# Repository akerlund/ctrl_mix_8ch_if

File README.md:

# ctrl_mix_8ch_if
An eight channel controller board for custom use

Each channel has one slider, two encoders, one switch and four LEDs. The PCB has got two potentiometers on each top corner and  4 LED bars for signal visualization. On the back there are analogue MUXes and LED drivers.

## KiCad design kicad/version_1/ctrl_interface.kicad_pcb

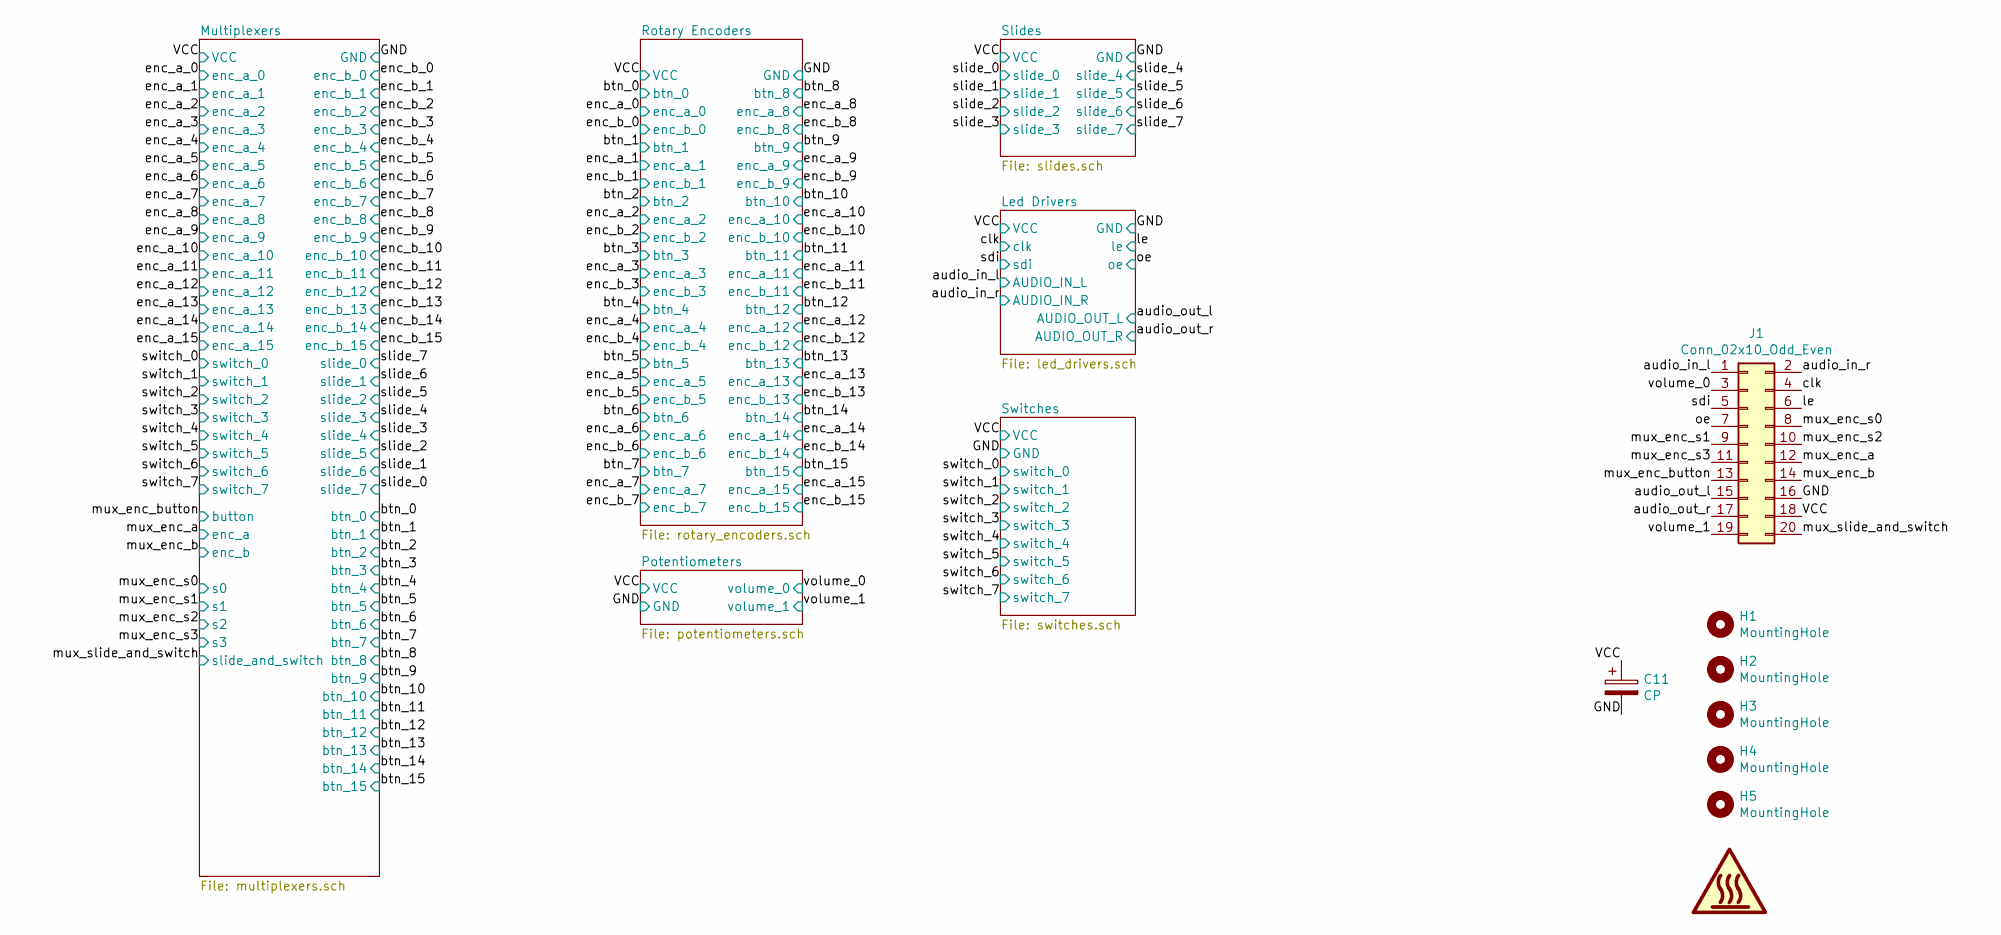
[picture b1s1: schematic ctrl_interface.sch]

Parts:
C11: CP; CP_Elec_5x5.7
H1, H2, H3, H4, H5: MountingHole; MountingHole_3mm_Pad_Via
J1: Conn_02x10_Odd_Even; PinSocket_2x10_P2.54mm_Vertical

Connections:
/GND: C11.2, J1.16; also elsewhere on the board
/VCC: C11.1, J1.18; also elsewhere on the board
/audio_in_l: J1.1; also elsewhere on the board
/audio_in_r: J1.2; also elsewhere on the board
/audio_out_l: J1.15; also elsewhere on the board
/audio_out_r: J1.17; also elsewhere on the board
/clk: J1.4; also elsewhere on the board
/le: J1.6; also elsewhere on the board
/mux_enc_a: J1.12; also elsewhere on the board
/mux_enc_b: J1.14; also elsewhere on the board
/mux_enc_button: J1.13; also elsewhere on the board
/mux_enc_s0: J1.8; also elsewhere on the board
/mux_enc_s1: J1.9; also elsewhere on the board
/mux_enc_s2: J1.10; also elsewhere on the board
/mux_enc_s3: J1.11; also elsewhere on the board
/mux_slide_and_switch: J1.20; also elsewhere on the board
/oe: J1.7; also elsewhere on the board
/sdi: J1.5; also elsewhere on the board
/volume_0: J1.3; also elsewhere on the board
/volume_1: J1.19; also elsewhere on the board

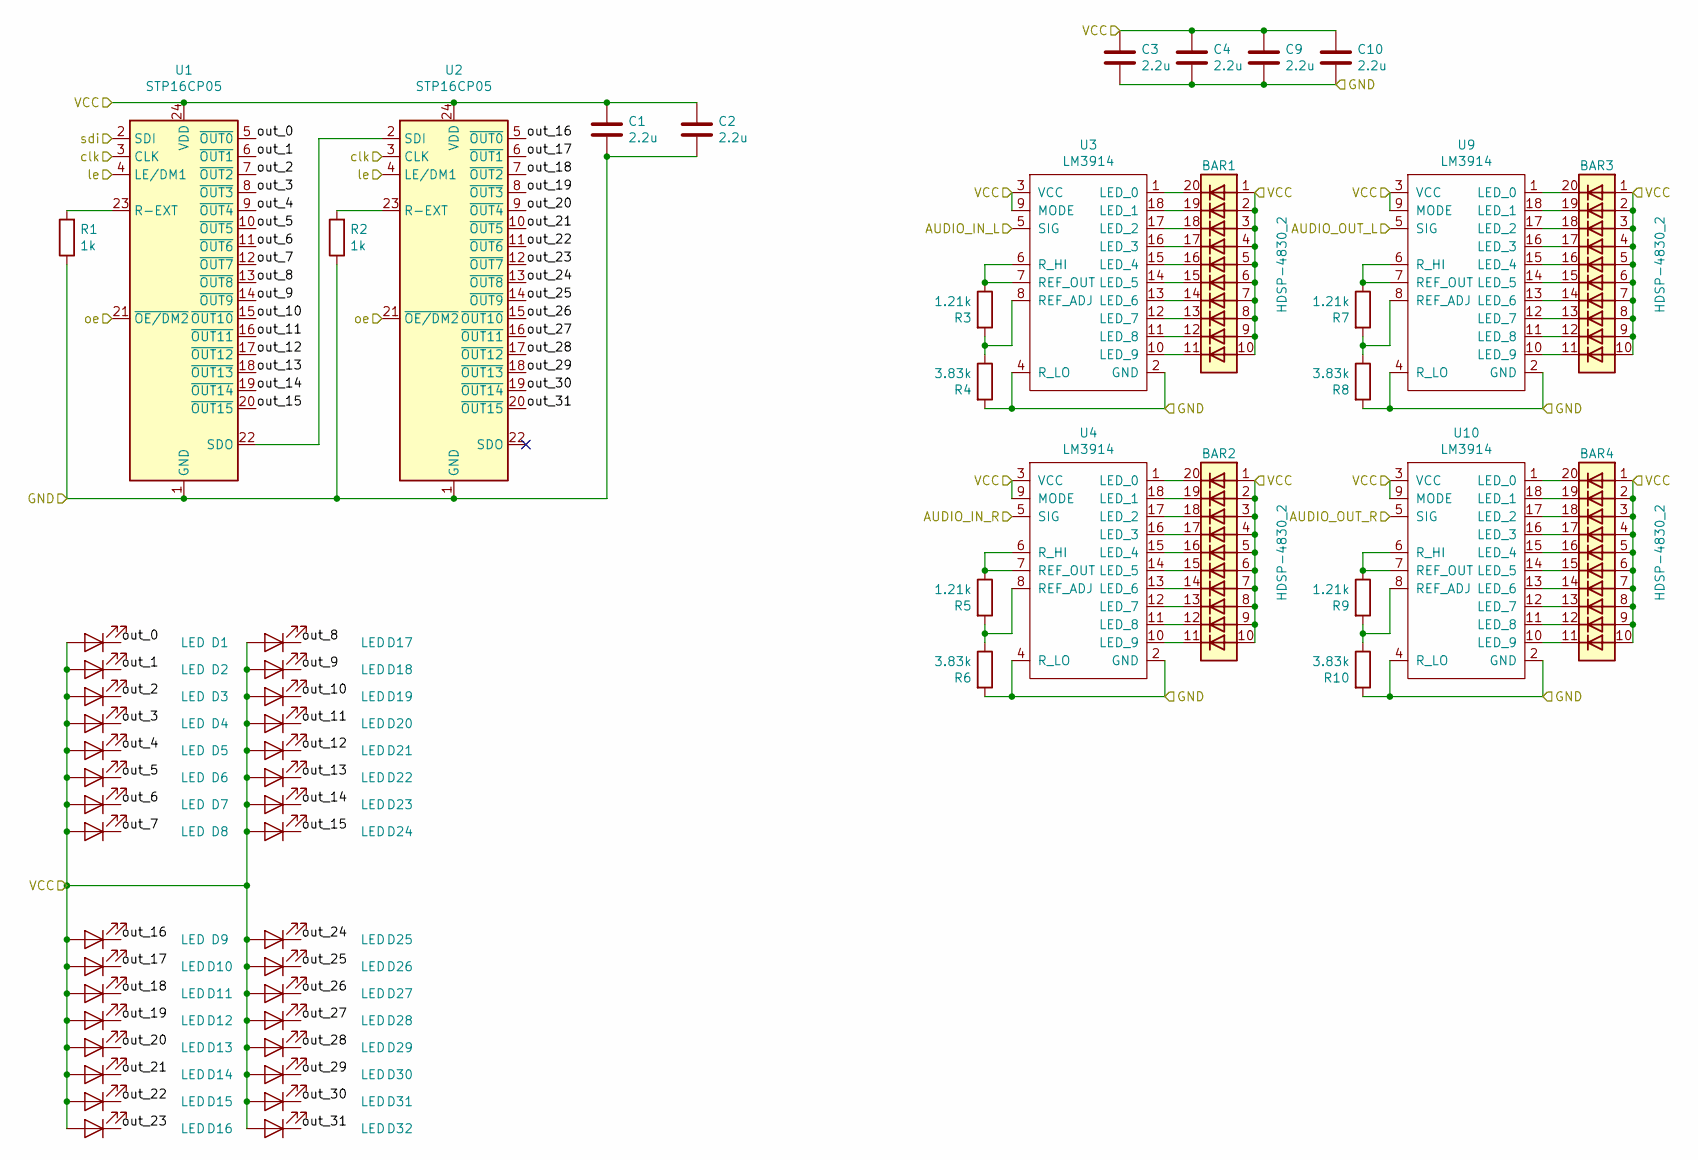
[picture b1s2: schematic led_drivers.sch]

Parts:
BAR1, BAR2, BAR3, BAR4: HDSP-4830_2; HDSP-4830
C1, C2, C3, C4, C9, C10: 2.2u; C_0603_1608Metric
D1, D2, D3, D4, D5, D6, D7, D8, D9, D10, D11, D12, D13, D14, D15, D16, D17, D18, D19, D20, D21, D22, D23, D24, D25, D26, D27, D28, D29, D30, D31, D32: LED; LED_0805_2012Metric
R1, R2: 1k; R_0603_1608Metric
R3, R5, R7, R9: 1.21k; R_0603_1608Metric
R4, R6, R8, R10: 3.83k; R_0603_1608Metric
U1, U2: STP16CP05; SSOP-24_3.9x8.7mm_P0.635mm
U3, U4, U9, U10: LM3914; DIP-18_W7.62mm

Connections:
/GND: C1.2, C2.2, C3.2, C4.2, C9.2, C10.2, R1.1, R2.1, R4.2, R6.2, R8.2, R10.2, U1.1 (GND), U2.1 (GND), U3.2 (GND), U3.4 (R_LO), U4.2 (GND), U4.4 (R_LO), U9.2 (GND), U9.4 (R_LO), U10.2 (GND), U10.4 (R_LO); also elsewhere on the board
/Led Drivers/out_0: D1.1 (K), U1.5 (~OUT0)
/Led Drivers/out_1: D2.1 (K), U1.6 (~OUT1)
/Led Drivers/out_2: D3.1 (K), U1.7 (~OUT2)
/Led Drivers/out_3: D4.1 (K), U1.8 (~OUT3)
/Led Drivers/out_4: D5.1 (K), U1.9 (~OUT4)
/Led Drivers/out_5: D6.1 (K), U1.10 (~OUT5)
/Led Drivers/out_6: D7.1 (K), U1.11 (~OUT6)
/Led Drivers/out_7: D8.1 (K), U1.12 (~OUT7)
/Led Drivers/out_8: D17.1 (K), U1.13 (~OUT8)
/Led Drivers/out_9: D18.1 (K), U1.14 (~OUT9)
/Led Drivers/out_10: D19.1 (K), U1.15 (~OUT10)
/Led Drivers/out_11: D20.1 (K), U1.16 (~OUT11)
/Led Drivers/out_12: D21.1 (K), U1.17 (~OUT12)
/Led Drivers/out_13: D22.1 (K), U1.18 (~OUT13)
/Led Drivers/out_14: D23.1 (K), U1.19 (~OUT14)
/Led Drivers/out_15: D24.1 (K), U1.20 (~OUT15)
/Led Drivers/out_16: D9.1 (K), U2.5 (~OUT0)
/Led Drivers/out_17: D10.1 (K), U2.6 (~OUT1)
/Led Drivers/out_18: D11.1 (K), U2.7 (~OUT2)
/Led Drivers/out_19: D12.1 (K), U2.8 (~OUT3)
/Led Drivers/out_20: D13.1 (K), U2.9 (~OUT4)
/Led Drivers/out_21: D14.1 (K), U2.10 (~OUT5)
/Led Drivers/out_22: D15.1 (K), U2.11 (~OUT6)
/Led Drivers/out_23: D16.1 (K), U2.12 (~OUT7)
/Led Drivers/out_24: D25.1 (K), U2.13 (~OUT8)
/Led Drivers/out_25: D26.1 (K), U2.14 (~OUT9)
/Led Drivers/out_26: D27.1 (K), U2.15 (~OUT10)
/Led Drivers/out_27: D28.1 (K), U2.16 (~OUT11)
/Led Drivers/out_28: D29.1 (K), U2.17 (~OUT12)
/Led Drivers/out_29: D30.1 (K), U2.18 (~OUT13)
/Led Drivers/out_30: D31.1 (K), U2.19 (~OUT14)
/Led Drivers/out_31: D32.1 (K), U2.20 (~OUT15)
/VCC: BAR1.1 (A), BAR1.2 (A), BAR1.3 (A), BAR1.4 (A), BAR1.5 (A), BAR1.6 (A), BAR1.7 (A), BAR1.8 (A), BAR1.9 (A), BAR1.10 (A), BAR2.1 (A), BAR2.2 (A), BAR2.3 (A), BAR2.4 (A), BAR2.5 (A), BAR2.6 (A), BAR2.7 (A), BAR2.8 (A), BAR2.9 (A), BAR2.10 (A), BAR3.1 (A), BAR3.2 (A), BAR3.3 (A), BAR3.4 (A), BAR3.5 (A), BAR3.6 (A), BAR3.7 (A), BAR3.8 (A), BAR3.9 (A), BAR3.10 (A), BAR4.1 (A), BAR4.2 (A), BAR4.3 (A), BAR4.4 (A), BAR4.5 (A), BAR4.6 (A), BAR4.7 (A), BAR4.8 (A), BAR4.9 (A), BAR4.10 (A), C1.1, C2.1, C3.1, C4.1, C9.1, C10.1, D1.2 (A), D2.2 (A), D3.2 (A), D4.2 (A), D5.2 (A), D6.2 (A), D7.2 (A), D8.2 (A), D9.2 (A), D10.2 (A), D11.2 (A), D12.2 (A), D13.2 (A), D14.2 (A), D15.2 (A), D16.2 (A), D17.2 (A), D18.2 (A), D19.2 (A), D20.2 (A), D21.2 (A), D22.2 (A), D23.2 (A), D24.2 (A), D25.2 (A), D26.2 (A), D27.2 (A), D28.2 (A), D29.2 (A), D30.2 (A), D31.2 (A), D32.2 (A), U1.24 (VDD), U2.24 (VDD), U3.3 (VCC), U3.9 (MODE), U4.3 (VCC), U4.9 (MODE), U9.3 (VCC), U9.9 (MODE), U10.3 (VCC), U10.9 (MODE); also elsewhere on the board
/audio_in_l: U3.5 (SIG); also elsewhere on the board
/audio_in_r: U4.5 (SIG); also elsewhere on the board
/audio_out_l: U9.5 (SIG); also elsewhere on the board
/audio_out_r: U10.5 (SIG); also elsewhere on the board
/clk: U1.3 (CLK), U2.3 (CLK); also elsewhere on the board
/le: U1.4 (LE/DM1), U2.4 (LE/DM1); also elsewhere on the board
/oe: U1.21 (~OE/DM2), U2.21 (~OE/DM2); also elsewhere on the board
/sdi: U1.2 (SDI); also elsewhere on the board
unnamed: BAR1.11 (K), U3.10 (LED_9)
unnamed: BAR1.12 (K), U3.11 (LED_8)
unnamed: BAR1.13 (K), U3.12 (LED_7)
unnamed: BAR1.14 (K), U3.13 (LED_6)
unnamed: BAR1.15 (K), U3.14 (LED_5)
unnamed: BAR1.16 (K), U3.15 (LED_4)
unnamed: BAR1.17 (K), U3.16 (LED_3)
unnamed: BAR1.18 (K), U3.17 (LED_2)
unnamed: BAR1.19 (K), U3.18 (LED_1)
unnamed: BAR1.20 (K), U3.1 (LED_0)
unnamed: BAR2.11 (K), U4.10 (LED_9)
unnamed: BAR2.12 (K), U4.11 (LED_8)
unnamed: BAR2.13 (K), U4.12 (LED_7)
unnamed: BAR2.14 (K), U4.13 (LED_6)
unnamed: BAR2.15 (K), U4.14 (LED_5)
unnamed: BAR2.16 (K), U4.15 (LED_4)
unnamed: BAR2.17 (K), U4.16 (LED_3)
unnamed: BAR2.18 (K), U4.17 (LED_2)
unnamed: BAR2.19 (K), U4.18 (LED_1)
unnamed: BAR2.20 (K), U4.1 (LED_0)
unnamed: BAR3.11 (K), U9.10 (LED_9)
unnamed: BAR3.12 (K), U9.11 (LED_8)
unnamed: BAR3.13 (K), U9.12 (LED_7)
unnamed: BAR3.14 (K), U9.13 (LED_6)
unnamed: BAR3.15 (K), U9.14 (LED_5)
unnamed: BAR3.16 (K), U9.15 (LED_4)
unnamed: BAR3.17 (K), U9.16 (LED_3)
unnamed: BAR3.18 (K), U9.17 (LED_2)
unnamed: BAR3.19 (K), U9.18 (LED_1)
unnamed: BAR3.20 (K), U9.1 (LED_0)
unnamed: BAR4.11 (K), U10.10 (LED_9)
unnamed: BAR4.12 (K), U10.11 (LED_8)
unnamed: BAR4.13 (K), U10.12 (LED_7)
unnamed: BAR4.14 (K), U10.13 (LED_6)
unnamed: BAR4.15 (K), U10.14 (LED_5)
unnamed: BAR4.16 (K), U10.15 (LED_4)
unnamed: BAR4.17 (K), U10.16 (LED_3)
unnamed: BAR4.18 (K), U10.17 (LED_2)
unnamed: BAR4.19 (K), U10.18 (LED_1)
unnamed: BAR4.20 (K), U10.1 (LED_0)
unnamed: R1.2, U1.23 (R-EXT)
unnamed: R2.2, U2.23 (R-EXT)
unnamed: R3.1, U3.6 (R_HI), U3.7 (REF_OUT)
unnamed: R3.2, R4.1, U3.8 (REF_ADJ)
unnamed: R5.1, U4.6 (R_HI), U4.7 (REF_OUT)
unnamed: R5.2, R6.1, U4.8 (REF_ADJ)
unnamed: R7.1, U9.6 (R_HI), U9.7 (REF_OUT)
unnamed: R7.2, R8.1, U9.8 (REF_ADJ)
unnamed: R9.1, U10.6 (R_HI), U10.7 (REF_OUT)
unnamed: R9.2, R10.1, U10.8 (REF_ADJ)
unnamed: U1.22 (SDO), U2.2 (SDI)

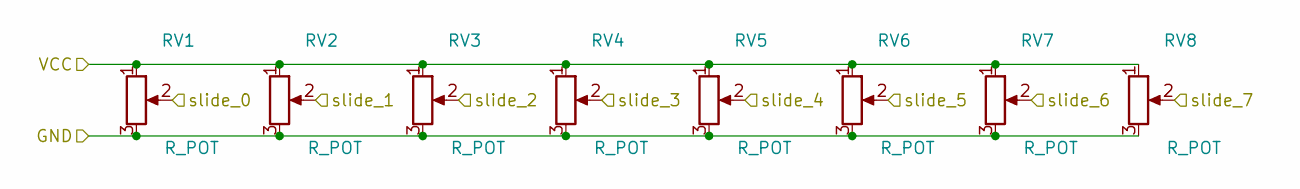
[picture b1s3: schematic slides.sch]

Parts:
RV1, RV2, RV3, RV4, RV5, RV6, RV7, RV8: R_POT; slide_pot_PS6010MA1B

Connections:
/GND: RV1.3, RV2.3, RV3.3, RV4.3, RV5.3, RV6.3, RV7.3, RV8.3; also elsewhere on the board
/VCC: RV1.1, RV2.1, RV3.1, RV4.1, RV5.1, RV6.1, RV7.1, RV8.1; also elsewhere on the board
/slide_0: RV1.2; also elsewhere on the board
/slide_1: RV2.2; also elsewhere on the board
/slide_2: RV3.2; also elsewhere on the board
/slide_3: RV4.2; also elsewhere on the board
/slide_4: RV5.2; also elsewhere on the board
/slide_5: RV6.2; also elsewhere on the board
/slide_6: RV7.2; also elsewhere on the board
/slide_7: RV8.2; also elsewhere on the board

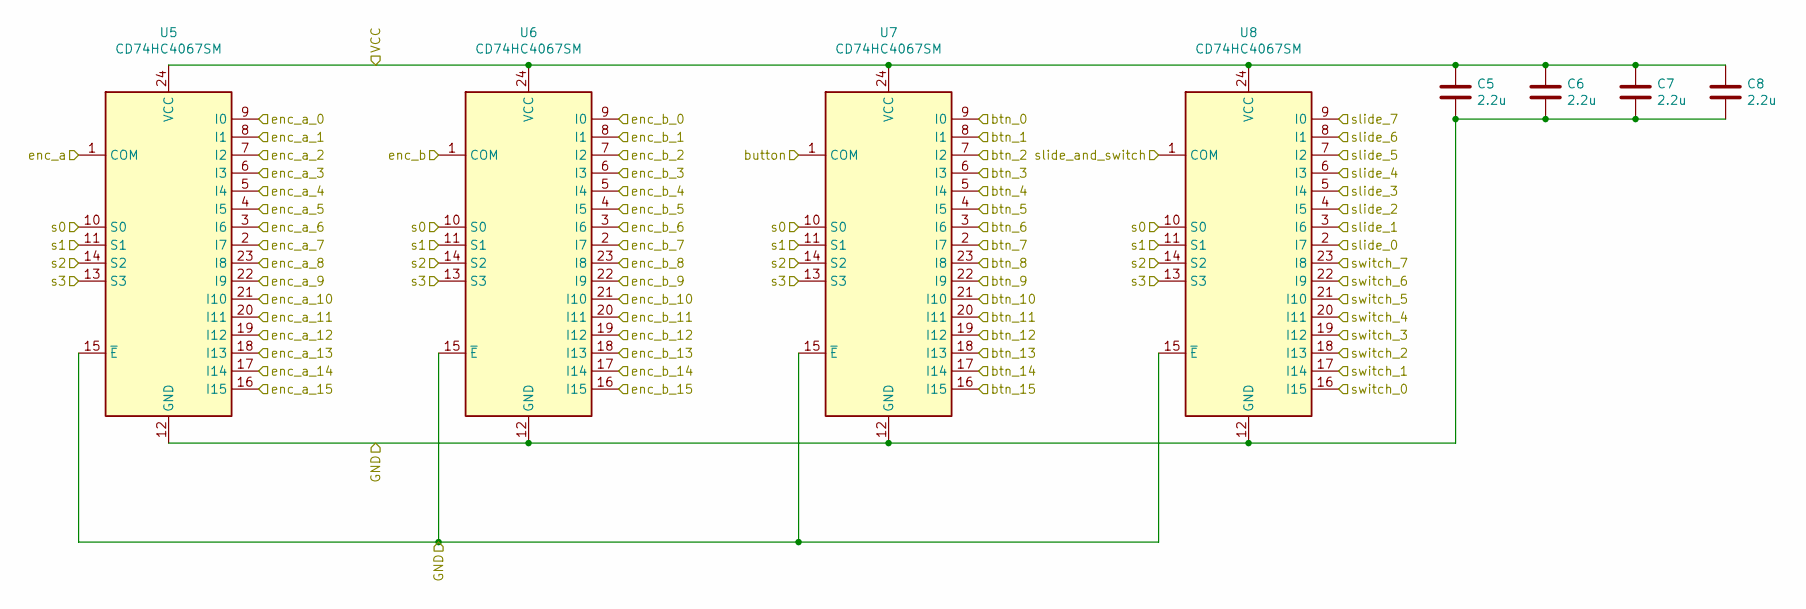
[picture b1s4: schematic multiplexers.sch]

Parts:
C5, C6, C7, C8: 2.2u; C_0603_1608Metric
U5, U6, U7, U8: CD74HC4067SM; SSOP-24_5.3x8.2mm_P0.65mm

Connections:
/GND: C5.2, C6.2, C7.2, C8.2, U5.12 (GND), U5.15 (~E), U6.12 (GND), U6.15 (~E), U7.12 (GND), U7.15 (~E), U8.12 (GND), U8.15 (~E); also elsewhere on the board
/VCC: C5.1, C6.1, C7.1, C8.1, U5.24 (VCC), U6.24 (VCC), U7.24 (VCC), U8.24 (VCC); also elsewhere on the board
/btn_0: U7.9 (I0); also elsewhere on the board
/btn_1: U7.8 (I1); also elsewhere on the board
/btn_2: U7.7 (I2); also elsewhere on the board
/btn_3: U7.6 (I3); also elsewhere on the board
/btn_4: U7.5 (I4); also elsewhere on the board
/btn_5: U7.4 (I5); also elsewhere on the board
/btn_6: U7.3 (I6); also elsewhere on the board
/btn_7: U7.2 (I7); also elsewhere on the board
/btn_8: U7.23 (I8); also elsewhere on the board
/btn_9: U7.22 (I9); also elsewhere on the board
/btn_10: U7.21 (I10); also elsewhere on the board
/btn_11: U7.20 (I11); also elsewhere on the board
/btn_12: U7.19 (I12); also elsewhere on the board
/btn_13: U7.18 (I13); also elsewhere on the board
/btn_14: U7.17 (I14); also elsewhere on the board
/btn_15: U7.16 (I15); also elsewhere on the board
/enc_a_0: U5.9 (I0); also elsewhere on the board
/enc_a_1: U5.8 (I1); also elsewhere on the board
/enc_a_2: U5.7 (I2); also elsewhere on the board
/enc_a_3: U5.6 (I3); also elsewhere on the board
/enc_a_4: U5.5 (I4); also elsewhere on the board
/enc_a_5: U5.4 (I5); also elsewhere on the board
/enc_a_6: U5.3 (I6); also elsewhere on the board
/enc_a_7: U5.2 (I7); also elsewhere on the board
/enc_a_8: U5.23 (I8); also elsewhere on the board
/enc_a_9: U5.22 (I9); also elsewhere on the board
/enc_a_10: U5.21 (I10); also elsewhere on the board
/enc_a_11: U5.20 (I11); also elsewhere on the board
/enc_a_12: U5.19 (I12); also elsewhere on the board
/enc_a_13: U5.18 (I13); also elsewhere on the board
/enc_a_14: U5.17 (I14); also elsewhere on the board
/enc_a_15: U5.16 (I15); also elsewhere on the board
/enc_b_0: U6.9 (I0); also elsewhere on the board
/enc_b_1: U6.8 (I1); also elsewhere on the board
/enc_b_2: U6.7 (I2); also elsewhere on the board
/enc_b_3: U6.6 (I3); also elsewhere on the board
/enc_b_4: U6.5 (I4); also elsewhere on the board
/enc_b_5: U6.4 (I5); also elsewhere on the board
/enc_b_6: U6.3 (I6); also elsewhere on the board
/enc_b_7: U6.2 (I7); also elsewhere on the board
/enc_b_8: U6.23 (I8); also elsewhere on the board
/enc_b_9: U6.22 (I9); also elsewhere on the board
/enc_b_10: U6.21 (I10); also elsewhere on the board
/enc_b_11: U6.20 (I11); also elsewhere on the board
/enc_b_12: U6.19 (I12); also elsewhere on the board
/enc_b_13: U6.18 (I13); also elsewhere on the board
/enc_b_14: U6.17 (I14); also elsewhere on the board
/enc_b_15: U6.16 (I15); also elsewhere on the board
/mux_enc_a: U5.1 (COM); also elsewhere on the board
/mux_enc_b: U6.1 (COM); also elsewhere on the board
/mux_enc_button: U7.1 (COM); also elsewhere on the board
/mux_enc_s0: U5.10 (S0), U6.10 (S0), U7.10 (S0), U8.10 (S0); also elsewhere on the board
/mux_enc_s1: U5.11 (S1), U6.11 (S1), U7.11 (S1), U8.11 (S1); also elsewhere on the board
/mux_enc_s2: U5.14 (S2), U6.14 (S2), U7.14 (S2), U8.14 (S2); also elsewhere on the board
/mux_enc_s3: U5.13 (S3), U6.13 (S3), U7.13 (S3), U8.13 (S3); also elsewhere on the board
/mux_slide_and_switch: U8.1 (COM); also elsewhere on the board
/slide_0: U8.9 (I0); also elsewhere on the board
/slide_1: U8.8 (I1); also elsewhere on the board
/slide_2: U8.7 (I2); also elsewhere on the board
/slide_3: U8.6 (I3); also elsewhere on the board
/slide_4: U8.5 (I4); also elsewhere on the board
/slide_5: U8.4 (I5); also elsewhere on the board
/slide_6: U8.3 (I6); also elsewhere on the board
/slide_7: U8.2 (I7); also elsewhere on the board
/switch_0: U8.16 (I15); also elsewhere on the board
/switch_1: U8.17 (I14); also elsewhere on the board
/switch_2: U8.18 (I13); also elsewhere on the board
/switch_3: U8.19 (I12); also elsewhere on the board
/switch_4: U8.20 (I11); also elsewhere on the board
/switch_5: U8.21 (I10); also elsewhere on the board
/switch_6: U8.22 (I9); also elsewhere on the board
/switch_7: U8.23 (I8); also elsewhere on the board

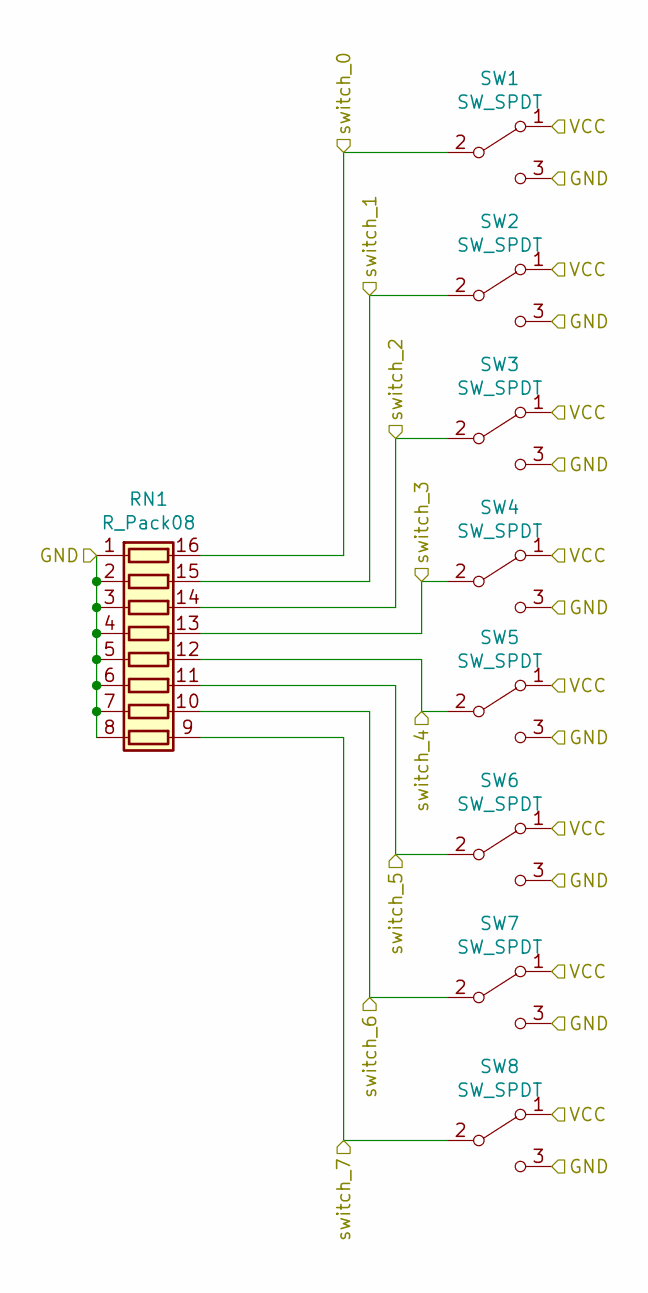
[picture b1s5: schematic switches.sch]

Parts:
RN1: R_Pack08; R_Array_Convex_8x0602
SW1, SW2, SW3, SW4, SW5, SW6, SW7, SW8: SW_SPDT; SW_Slide_1P2T_CK_OS102011MS2Q

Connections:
/GND: RN1.1 (R1.1), RN1.2 (R2.1), RN1.3 (R3.1), RN1.4 (R4.1), RN1.5 (R5.1), RN1.6 (R6.1), RN1.7 (R7.1), RN1.8 (R8.1), SW1.3 (C), SW2.3 (C), SW3.3 (C), SW4.3 (C), SW5.3 (C), SW6.3 (C), SW7.3 (C), SW8.3 (C); also elsewhere on the board
/VCC: SW1.1 (A), SW2.1 (A), SW3.1 (A), SW4.1 (A), SW5.1 (A), SW6.1 (A), SW7.1 (A), SW8.1 (A); also elsewhere on the board
/switch_0: RN1.16 (R1.2), SW1.2 (B); also elsewhere on the board
/switch_1: RN1.15 (R2.2), SW2.2 (B); also elsewhere on the board
/switch_2: RN1.14 (R3.2), SW3.2 (B); also elsewhere on the board
/switch_3: RN1.13 (R4.2), SW4.2 (B); also elsewhere on the board
/switch_4: RN1.12 (R5.2), SW5.2 (B); also elsewhere on the board
/switch_5: RN1.11 (R6.2), SW6.2 (B); also elsewhere on the board
/switch_6: RN1.10 (R7.2), SW7.2 (B); also elsewhere on the board
/switch_7: RN1.9 (R8.2), SW8.2 (B); also elsewhere on the board

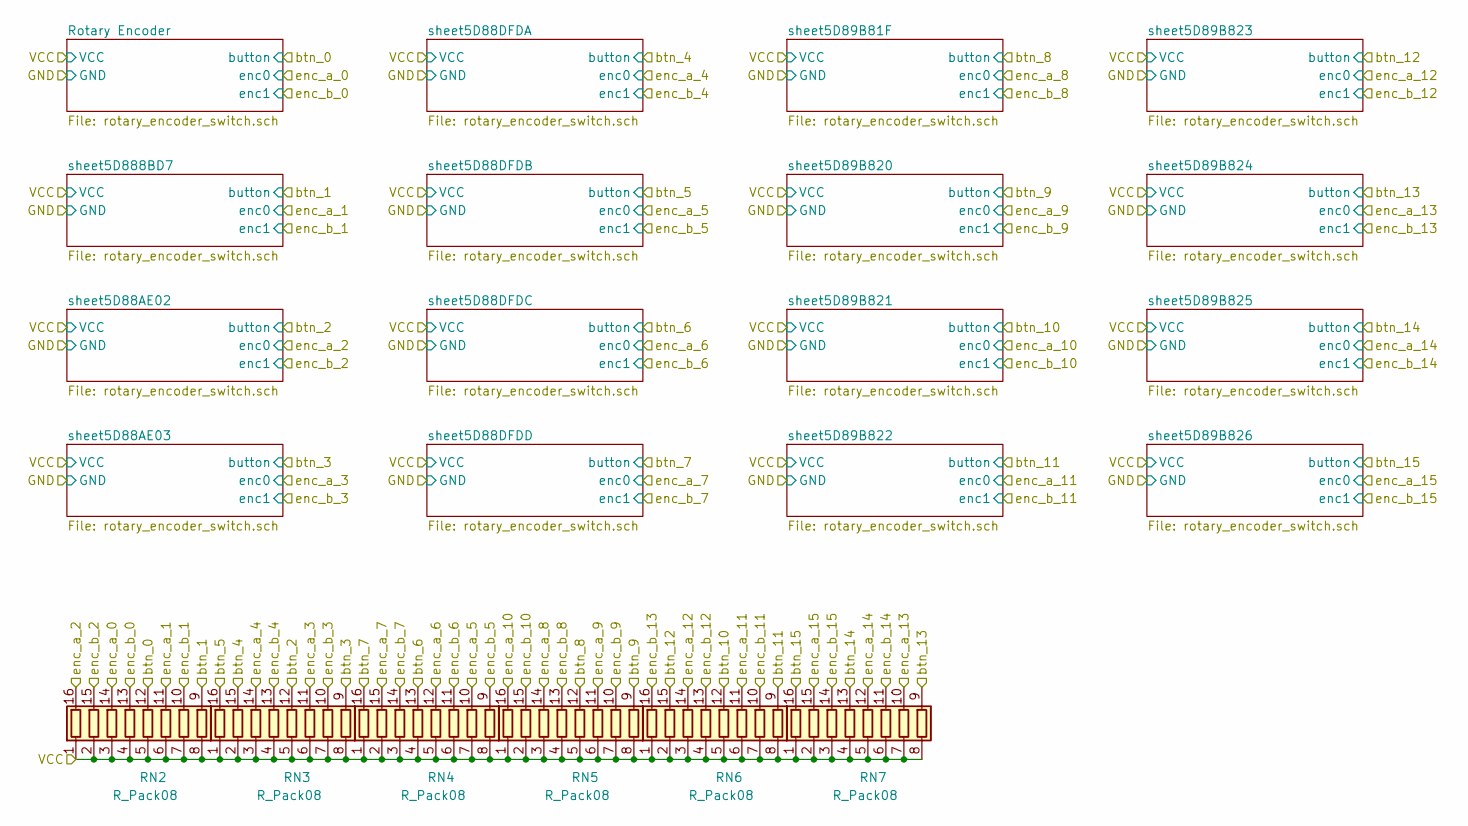
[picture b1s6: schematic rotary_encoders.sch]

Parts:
RN2, RN3, RN4, RN5, RN6, RN7: R_Pack08; R_Array_Convex_8x0602

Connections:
/VCC: RN2.1 (R1.1), RN2.2 (R2.1), RN2.3 (R3.1), RN2.4 (R4.1), RN2.5 (R5.1), RN2.6 (R6.1), RN2.7 (R7.1), RN2.8 (R8.1), RN3.1 (R1.1), RN3.2 (R2.1), RN3.3 (R3.1), RN3.4 (R4.1), RN3.5 (R5.1), RN3.6 (R6.1), RN3.7 (R7.1), RN3.8 (R8.1), RN4.1 (R1.1), RN4.2 (R2.1), RN4.3 (R3.1), RN4.4 (R4.1), RN4.5 (R5.1), RN4.6 (R6.1), RN4.7 (R7.1), RN4.8 (R8.1), RN5.1 (R1.1), RN5.2 (R2.1), RN5.3 (R3.1), RN5.4 (R4.1), RN5.5 (R5.1), RN5.6 (R6.1), RN5.7 (R7.1), RN5.8 (R8.1), RN6.1 (R1.1), RN6.2 (R2.1), RN6.3 (R3.1), RN6.4 (R4.1), RN6.5 (R5.1), RN6.6 (R6.1), RN6.7 (R7.1), RN6.8 (R8.1), RN7.1 (R1.1), RN7.2 (R2.1), RN7.3 (R3.1), RN7.4 (R4.1), RN7.5 (R5.1), RN7.6 (R6.1), RN7.7 (R7.1), RN7.8 (R8.1); also elsewhere on the board
/btn_0: RN2.12 (R5.2); also elsewhere on the board
/btn_1: RN2.9 (R8.2); also elsewhere on the board
/btn_2: RN3.12 (R5.2); also elsewhere on the board
/btn_3: RN3.9 (R8.2); also elsewhere on the board
/btn_4: RN3.15 (R2.2); also elsewhere on the board
/btn_5: RN3.16 (R1.2); also elsewhere on the board
/btn_6: RN4.13 (R4.2); also elsewhere on the board
/btn_7: RN4.16 (R1.2); also elsewhere on the board
/btn_8: RN5.12 (R5.2); also elsewhere on the board
/btn_9: RN5.9 (R8.2); also elsewhere on the board
/btn_10: RN6.12 (R5.2); also elsewhere on the board
/btn_11: RN6.9 (R8.2); also elsewhere on the board
/btn_12: RN6.15 (R2.2); also elsewhere on the board
/btn_13: RN7.9 (R8.2); also elsewhere on the board
/btn_14: RN7.13 (R4.2); also elsewhere on the board
/btn_15: RN7.16 (R1.2); also elsewhere on the board
/enc_a_0: RN2.14 (R3.2); also elsewhere on the board
/enc_a_1: RN2.11 (R6.2); also elsewhere on the board
/enc_a_2: RN2.16 (R1.2); also elsewhere on the board
/enc_a_3: RN3.11 (R6.2); also elsewhere on the board
/enc_a_4: RN3.14 (R3.2); also elsewhere on the board
/enc_a_5: RN4.10 (R7.2); also elsewhere on the board
/enc_a_6: RN4.12 (R5.2); also elsewhere on the board
/enc_a_7: RN4.15 (R2.2); also elsewhere on the board
/enc_a_8: RN5.14 (R3.2); also elsewhere on the board
/enc_a_9: RN5.11 (R6.2); also elsewhere on the board
/enc_a_10: RN5.16 (R1.2); also elsewhere on the board
/enc_a_11: RN6.11 (R6.2); also elsewhere on the board
/enc_a_12: RN6.14 (R3.2); also elsewhere on the board
/enc_a_13: RN7.10 (R7.2); also elsewhere on the board
/enc_a_14: RN7.12 (R5.2); also elsewhere on the board
/enc_a_15: RN7.15 (R2.2); also elsewhere on the board
/enc_b_0: RN2.13 (R4.2); also elsewhere on the board
/enc_b_1: RN2.10 (R7.2); also elsewhere on the board
/enc_b_2: RN2.15 (R2.2); also elsewhere on the board
/enc_b_3: RN3.10 (R7.2); also elsewhere on the board
/enc_b_4: RN3.13 (R4.2); also elsewhere on the board
/enc_b_5: RN4.9 (R8.2); also elsewhere on the board
/enc_b_6: RN4.11 (R6.2); also elsewhere on the board
/enc_b_7: RN4.14 (R3.2); also elsewhere on the board
/enc_b_8: RN5.13 (R4.2); also elsewhere on the board
/enc_b_9: RN5.10 (R7.2); also elsewhere on the board
/enc_b_10: RN5.15 (R2.2); also elsewhere on the board
/enc_b_11: RN6.10 (R7.2); also elsewhere on the board
/enc_b_12: RN6.13 (R4.2); also elsewhere on the board
/enc_b_13: RN6.16 (R1.2); also elsewhere on the board
/enc_b_14: RN7.11 (R6.2); also elsewhere on the board
/enc_b_15: RN7.14 (R3.2); also elsewhere on the board

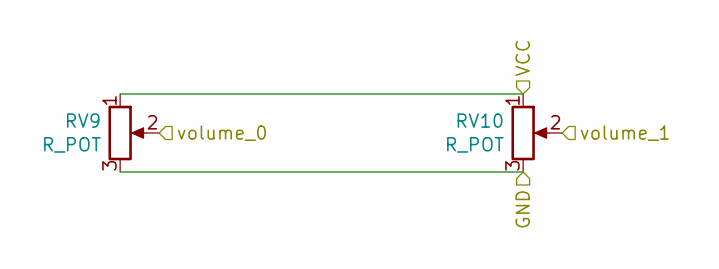
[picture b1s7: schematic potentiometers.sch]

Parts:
RV9, RV10: R_POT; Potentiometer_Alpha_RD901F-40-00D_Single_Vertical

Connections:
/GND: RV9.3, RV10.3; also elsewhere on the board
/VCC: RV9.1, RV10.1; also elsewhere on the board
/volume_0: RV9.2; also elsewhere on the board
/volume_1: RV10.2; also elsewhere on the board

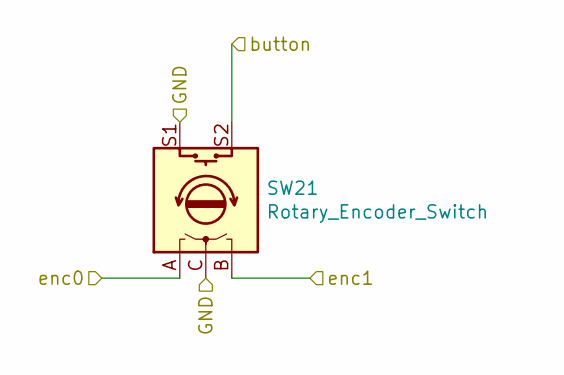
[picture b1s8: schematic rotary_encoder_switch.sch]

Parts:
SW9: Rotary_Encoder_Switch; RotaryEncoder_Alps_EC11E-Switch_Vertical_H20mm

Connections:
/GND: SW9.C, SW9.S1; also elsewhere on the board
/btn_0: SW9.S2; also elsewhere on the board
/enc_a_0: SW9.A; also elsewhere on the board
/enc_b_0: SW9.B; also elsewhere on the board

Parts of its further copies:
SW10, SW11, SW12, SW13, SW14, SW15, SW16, SW17, SW18, SW19, SW20, SW21, SW22, SW23, SW24: Rotary_Encoder_Switch; RotaryEncoder_Alps_EC11E-Switch_Vertical_H20mm

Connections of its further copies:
/GND: SW10.C, SW10.S1, SW11.C, SW11.S1, SW12.C, SW12.S1, SW13.C, SW13.S1, SW14.C, SW14.S1, SW15.C, SW15.S1, SW16.C, SW16.S1, SW17.C, SW17.S1, SW18.C, SW18.S1, SW19.C, SW19.S1, SW20.C, SW20.S1, SW21.C, SW21.S1, SW22.C, SW22.S1, SW23.C, SW23.S1, SW24.C, SW24.S1; also elsewhere on the board
/btn_1: SW10.S2; also elsewhere on the board
/btn_2: SW11.S2; also elsewhere on the board
/btn_3: SW12.S2; also elsewhere on the board
/btn_4: SW13.S2; also elsewhere on the board
/btn_5: SW14.S2; also elsewhere on the board
/btn_6: SW15.S2; also elsewhere on the board
/btn_7: SW16.S2; also elsewhere on the board
/btn_8: SW17.S2; also elsewhere on the board
/btn_9: SW18.S2; also elsewhere on the board
/btn_10: SW19.S2; also elsewhere on the board
/btn_11: SW20.S2; also elsewhere on the board
/btn_12: SW21.S2; also elsewhere on the board
/btn_13: SW22.S2; also elsewhere on the board
/btn_14: SW23.S2; also elsewhere on the board
/btn_15: SW24.S2; also elsewhere on the board
/enc_a_1: SW10.A; also elsewhere on the board
/enc_a_2: SW11.A; also elsewhere on the board
/enc_a_3: SW12.A; also elsewhere on the board
/enc_a_4: SW13.A; also elsewhere on the board
/enc_a_5: SW14.A; also elsewhere on the board
/enc_a_6: SW15.A; also elsewhere on the board
/enc_a_7: SW16.A; also elsewhere on the board
/enc_a_8: SW17.A; also elsewhere on the board
/enc_a_9: SW18.A; also elsewhere on the board
/enc_a_10: SW19.A; also elsewhere on the board
/enc_a_11: SW20.A; also elsewhere on the board
/enc_a_12: SW21.A; also elsewhere on the board
/enc_a_13: SW22.A; also elsewhere on the board
/enc_a_14: SW23.A; also elsewhere on the board
/enc_a_15: SW24.A; also elsewhere on the board
/enc_b_1: SW10.B; also elsewhere on the board
/enc_b_2: SW11.B; also elsewhere on the board
/enc_b_3: SW12.B; also elsewhere on the board
/enc_b_4: SW13.B; also elsewhere on the board
/enc_b_5: SW14.B; also elsewhere on the board
/enc_b_6: SW15.B; also elsewhere on the board
/enc_b_7: SW16.B; also elsewhere on the board
/enc_b_8: SW17.B; also elsewhere on the board
/enc_b_9: SW18.B; also elsewhere on the board
/enc_b_10: SW19.B; also elsewhere on the board
/enc_b_11: SW20.B; also elsewhere on the board
/enc_b_12: SW21.B; also elsewhere on the board
/enc_b_13: SW22.B; also elsewhere on the board
/enc_b_14: SW23.B; also elsewhere on the board
/enc_b_15: SW24.B; also elsewhere on the board

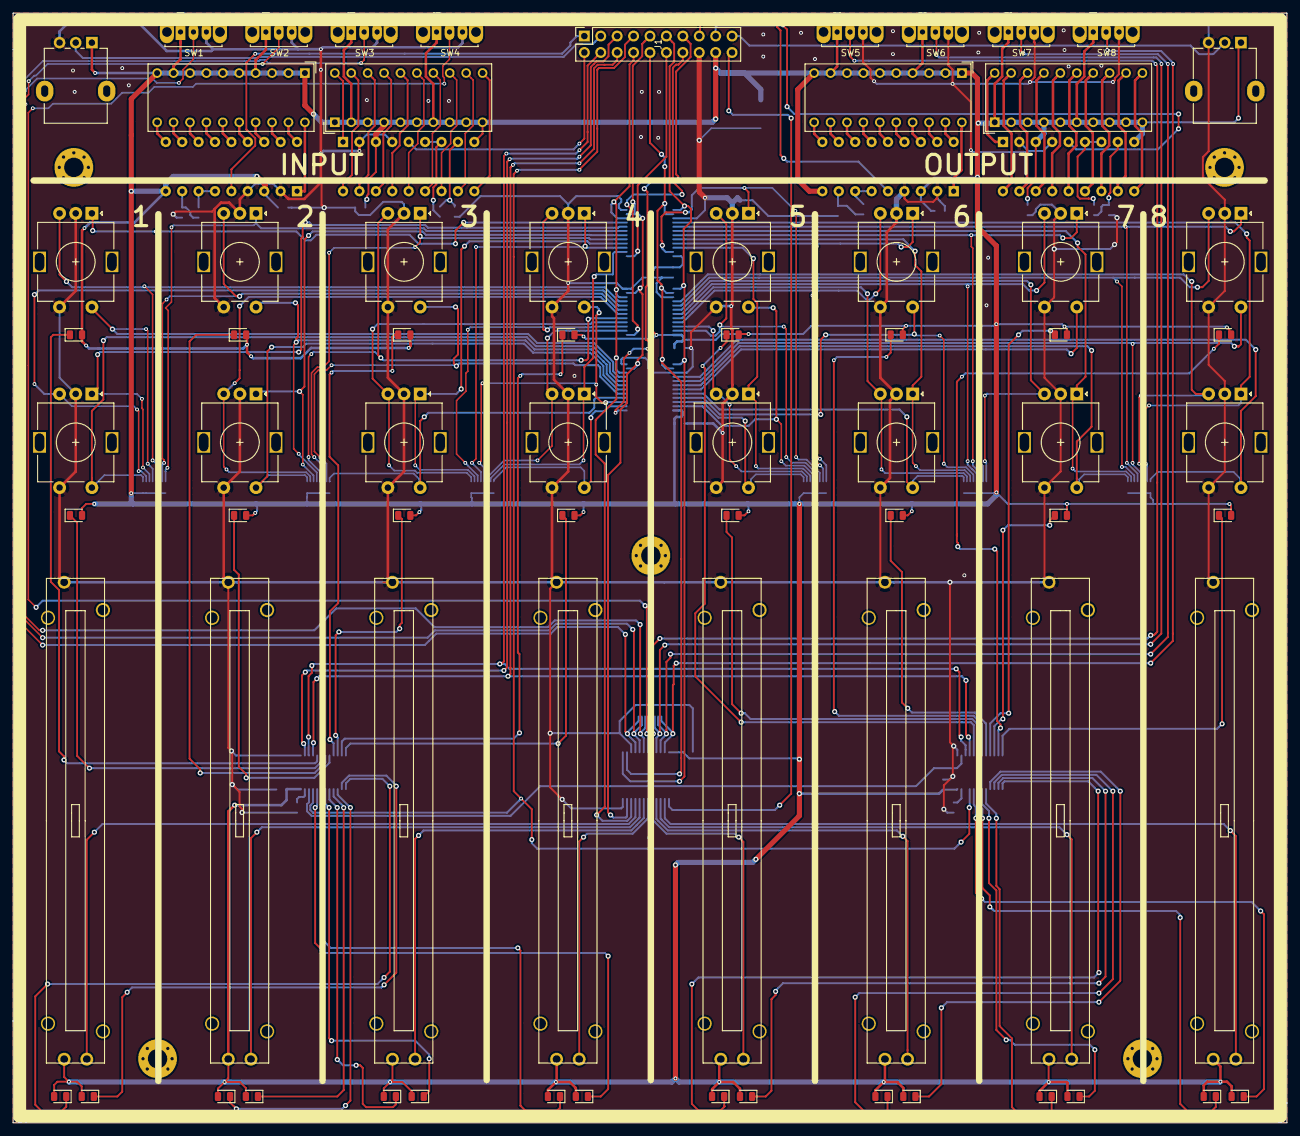
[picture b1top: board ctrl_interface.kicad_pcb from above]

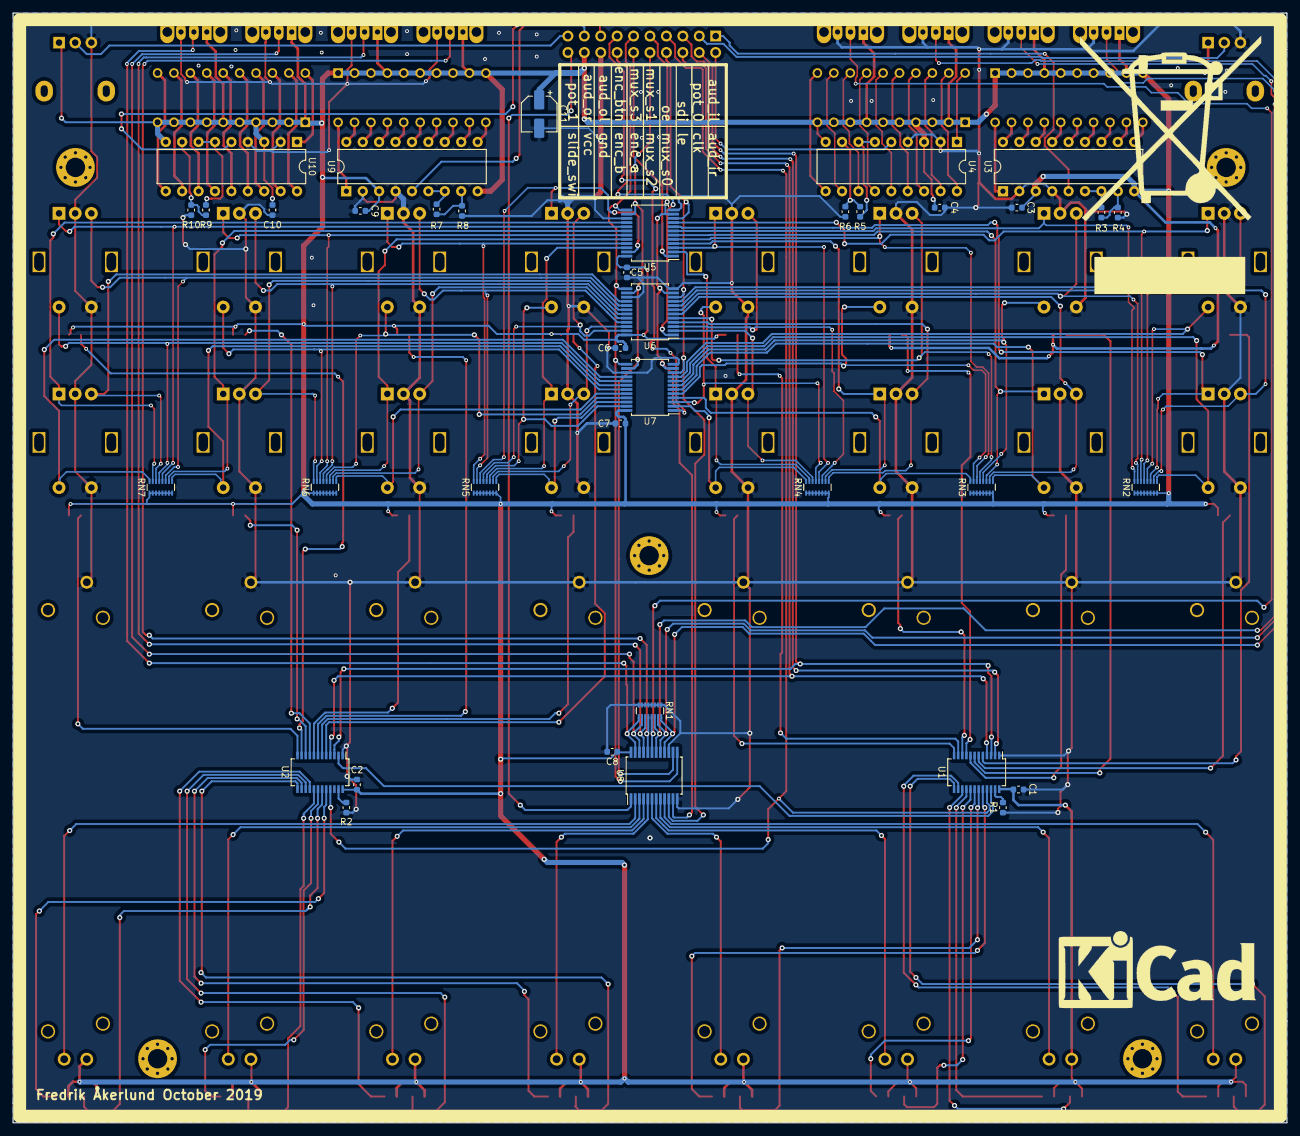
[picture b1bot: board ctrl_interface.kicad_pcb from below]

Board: 2 copper layers, 197.1 x 171.7 mm, 114 parts (38 on the bottom side), 167 nets.

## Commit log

2019-12-27 Upload first version of the PCB
